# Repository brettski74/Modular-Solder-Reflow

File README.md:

# Modular-Solder-Reflow
Modular designs for a DIY solder reflow hotplate, controller, power supply and more.

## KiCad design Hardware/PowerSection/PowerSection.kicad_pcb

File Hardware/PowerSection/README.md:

# Power Section Design

This directory contains a design for the main power control section of a reflow hotplate. The design is based on a buck converter with a low side switch. It includes current sensing via two INA180 current sense amplifiers. The PWM signal is provided externally. The main goals of the current design are:

  - Verify the design works.
  - Reduce current ripple and voltage spikes to manageable levels.
  - Allow high frequency operation without making input capacitors or other components excessively hot.
  - Allow testing of different microcontroller, screen and UI combinations with a working power section.
  - Provide up to 100W of output power.
  - Be able to operate from power supplies ranging from 12V to 20V DC.

## How to Use This Module

This module provides the power section of a hotplate only. It provides a means for efficient power conversion. It does not supply the control system (ie. microcontroller and firmware), the user interface (eg. screen and buttons or rotary encoder) or the load (ie. the heating element). You need to provide these. Further modules will become availableas the design progresses, although the modular nature also means that you can provide your own.

### Heat Considerations

While care has been taken to design a reasonably efficient design and use components rated for the required currents and they have been mounted with ample board space to help dissipate any heat, this module does handle reasonably large amounts of power. Some of that power will be dissipated in parts of the board and so it may get warm. The board is not yet tested, so you should take appropriate care when testing the board for your own needs and monitor the temperature of its components until you're satisfied that it can adequately handle the heat for your use case.

### Connections

The module includes the following connections:

|| Connector   | Pin  | Description |
| :--- | :---        | :--- | :---        |
|| Barrel Jack |      | Input power. 12V minimum. 18-20V preferred. Note that the Digikey part is rated for up to 8A. The LCSC part is rated for up to 7A. 5.5 x 2.5mm barrel connector. Centre pin positive.|
|| 12-20V      |      | Alternate connection for external power positive terminal via an M3 ring connector or similar. |
|| GND         |      | Alternate connection for external power negative terminal via an M3 ring connector or similar. Grounded. |
|| Htr+        |      | Positive connection for the heating element. |
|| Htr-        |      | Negative connection for the heating element. Note that this is not grounded and must not be connected to the ground connections of this board. |
|<td rowspan=5>J1</td>| PWM  | PWM signal. The gate driver is inverting, so the PWM signal must be active low. When the PWM signal is below about 0.8V, the main MOSFET switch will be on. When this voltage is above about 2.5V, the main MOSFET switch will be off. It does have a 10k pullup to _Vin_, so if left floating should ensure that the main MOSFET switch is off. |
|| Vin  | Supply voltage for the control board. This is used to power current sense and pullups for the gate drive input to ensure compatibility with the microcontroller. Must be between 3.0 and 5.5V. |
|| Ihi  | Current sense output for heating element current used for measuring high magnitude currents. Assuming a 15 $m\Omega$ shunt, voltage should be approximately $V_{Ilo} = 0.015 \times 20 \times I_{htr}$. Output is limited to approximately _Vin_. |
|| Ilo  | Current sense output for heating element current used for measuring low magnitude currents. Assuming a 15 $m\Omega$ shunt, voltage should be approximately $V_{Ilo} = 0.015 \times 200 \times I_{htr}$. Output is limited to approximately _Vin_. |
|| GND  | Ground connection for control board. |
|<td rowspan=5>J2</td>| VS   | Auxiliary connection for supplying power to external boards. This is not intended as an input pin and cannot safely supply the power requirements of the heating element. It is intended as an output to potentially feed power to other boards that may require it. For example, if you don't have some other power supply for your control board, you could feed this into a 3 terminal regulator to provide a steady 5V or 3.3V supply to your control board. |
|| GND  | Auxiliary ground connection for supplying power to external boards. The same power limitations and expected uses for _J2-VS_ also apply to this pin. |

A basic diagram of minimal connections to this module is shown below. A more typical setup would may also include additional items such as a screen, buttons/rotary encoder for input, voltage divider for measuring input voltage, thermistor or other temperature sensor connections and the like.

### Hotplates

The modular design of this board requires that you supply a separate hotplate. While this does mean that you have more separate pieces to connect and potential higher expense to have them produced, it does provide the following advantages:

  - Larger size/lower cost. If working with the cheap Chinese based board manufacturers like JLCPCB, PCBWay, Elecrow and the like, prices are extremely cheap if you can keep under 100mm x 100mm in size. With this pricing, you should be able to produce a board like this plus a 100mm x 100mm hotplate board more cheaply than you could have an integrated board with a hotplate this size included. The integrated board therefore either requires more money or must sacrifice hotplate size to stay cheap.
  - Replaceable hotplate. While it's still unclear just how durable PCB based hotplates may be, we do expect them to eventually wear out from the thermal cycling they will be put through. Having a separate hotplate PCB with minimal electronics attached makes them easier and cheaper to replace when they do wear out.
  - Thermal isolation. A separate hotplate PCB can be more easily and more effectively isolated from the rest of the system without the need to take up valuable board space with cut-outs or other design features to keep the heat of the hotplate away from control and user interface components.

The power module connects to the hotplate via two M3 ring connector terminals on the right side of the board. These can also be used as mounting holes for the board provided that they are being mounted into a non-conductive base. A suggested option is to use a 3D printed base of some sort in ABS or PLA. Care should be taken to ensure sufficient thermal isolation of the base from heat that may be produced in the power module and the hotplate. 

Cables connecting the power module and hotplate should be of sufficient weight to handle the currents involved. They should also use appropriate insulation to handle any thermal leakage from the hotplate into the wires. A minimum suggested spec would be 16AWG stranded copper wire with silicone insulation.

It is recommended to use mechanical connectors for the connections to your hotplate as well. M3 ring connectors are my preferred solution. These avoid problems with plastic or soldered connections which may melt from the heat of the hotplate. After all, the hotplate is intended to get hot enough to melt various solder alloys.

If you currently have spare boards from building a V2.4 or V3.0 board of the AfterEarthLtd hotplate design, you can use one of those as an external hotplate for this board if you have nothing better. You can connect wires directly to the heating element by soldering them onto the board. One should connect to the MOSFET drain terminal (the large one). The other should connect to lower terminal (ie. closest to the heating element) of either C7, D2 or both. If possible, use a higher temperature solder alloy for these connections such as SAC305 (the usual lead-free alloy of tin-silver-copper used in electronics). This should help prevent these connections from desoldering themselves during a reflow cycle.

### Controller

The current design does not yet include a controller. You will need to provide your own. In the absence of a more bespoke design, the suggestion is to use a typical prototyping board like one of the various Arduino modules, Seeeduino Xiao, STM32 Blue Pill, WEMOS S2 Mini or similar boards. My original work with this module will work with Arduino Nano, Seeeduino Xiao and Blue Pill boards. I have most experience with the Nano and the Xiao, although my long term goal is to use STM32 microcontrollers for controlling these hotplates. My plan is to make the firmware modular as well and easily ported to different microcontroller platforms, sensor suites and user interfaces. Until that is done, you are welcome to experiment with this board and with building your own firmware.

J1 should provide most of the connections you may require for the microcontroller to this power module. It is designed as a 5 pin JST-XH connector or compatible. Alternatively, you could also use a 0.1" pin header for connection if you already have those conveniently available. The _PWM_, _Vin_ and _GND_ pins must be connected. _Ihi_ and _Ilo_ can be used for sensing the heating element currents which can be used in conjunction with the heating element voltage to deduce heating element resistance and use it as a temperature sensor. If you also wish to monitor supply voltage, you can feed J2 to an off-board voltage divider to measure that as well. These connections should all be low current/power and should be possible to build on a solderless breadboard for prototyping purposes.

## Theory Of Operation

In addition to the main power input, this board expects a PWM signal at a frequency between 60kHz and 200kHz. The gate drive circuitry is inverting, so the PWM pin is active low. Users must bear this in mind when developing software to control this board. The PWM signal can operate on 3.3V or 5V. It is first fed into MOSFET Q1, which provides level shifting in conjunction with R5. This pulls the PWM signal up to near the main power supply voltage. This is one of the reasons for the 20V upper limit on the input voltage. Most MOSFETs are limited to about 20V on their gate.

The level shifted PWM signal is then fed into a totem pole gate driver (U4) to drive larger currents into Q2's gate. Q2 is the main MOSFET switch. When the PWM signal goes low, Q2's gate is driven high, turning it on. Once Q2 turns on, it pulls current through the heating element and L2. When the PWM signal goes high again, Q2's gate is pulled low, turning it off. Diode D3 now starts to conduct providing a conduction path for the current in L2. L2 limits current ripple in the heater circuit. Capacitor C9 reduces voltage ripple.

C8 and R10 form an RC snubber across the main MOSFET switch. Component values are approximate and not specifically tuned for this design yet. That said, it is expected that they should function adequately for the task. There is also an RC snubber across D3 formed by R8 and C7.

Resistors R11, R12 and R13 form a current shunt for measuring the current through the heating element. The three 45m$\Omega$ resistors form a 15m$\Omega$ shunt. These resistors should have a low temperature coefficient of resistance. Three 2W resistors are specified to provide ample headroom to dissipate heat when operating at high currents - as may be necessary for 12V supplies.

The design includes two current sense amplifiers with different gains to allow for full range current sensing while also allowing higher resolution at lower currents. The current sense amplifier outputs have a low pass filter on their outputs formed by R1/C3 and R2/C4. As designed, these have a corner frequency at about 1.6kHz. It is assumed that PID control would use a sample frequency somewhere in the vicinity of 20-50Hz,

The input currently includes a 10 amp fuse to protect against overcurrent faults. It also includes an input LC filter to help limit upstream impacts from the operation of the heater control.

## Optional Components

The RC snubbers formed by C8/R10 and C7/R8 are not entirely necessary for the ciruit to work, however, they should reduce ringing and other transient effects from the high frequency switching of large currents.

Diode D1 provides a lower impedance path for discharge Q2's gate at turn-off time. While this is usually desirable, the circuit will likely work ok without it.

If you have no intention of measuring the heater current, you can omit the INA180 current sense amplified and associated buffer and filter components. You do need to either include R11, R12 and R13 or alternatively short them with some wire suitable for the current you expect to drive with this board.

Inductor L1 may not ne necessary. It's main purpose is to reduce the amount of noise fed back to the upstream power supply, however, the board will likely work relatively fine without it. If not used, simply short the contacts for L2 with some wire.

## 3D Models

To render a 3D representation of the board and components, some of the footprints require 3D models that are not available with KiCad and are also not included in the git repository. There are freely available 3D models for these components, but since I'm not sure of the licensing of these models, I'm reluctant to include them and effectively be redistributing them in my git repository. Instead, I've included a shell script in the 3d subdirectory that will download the models from publicly accessible locations on the web for you to use for your own needs. If you don't care about a 3D rendering of the board and components, then you don't need these 3D models.

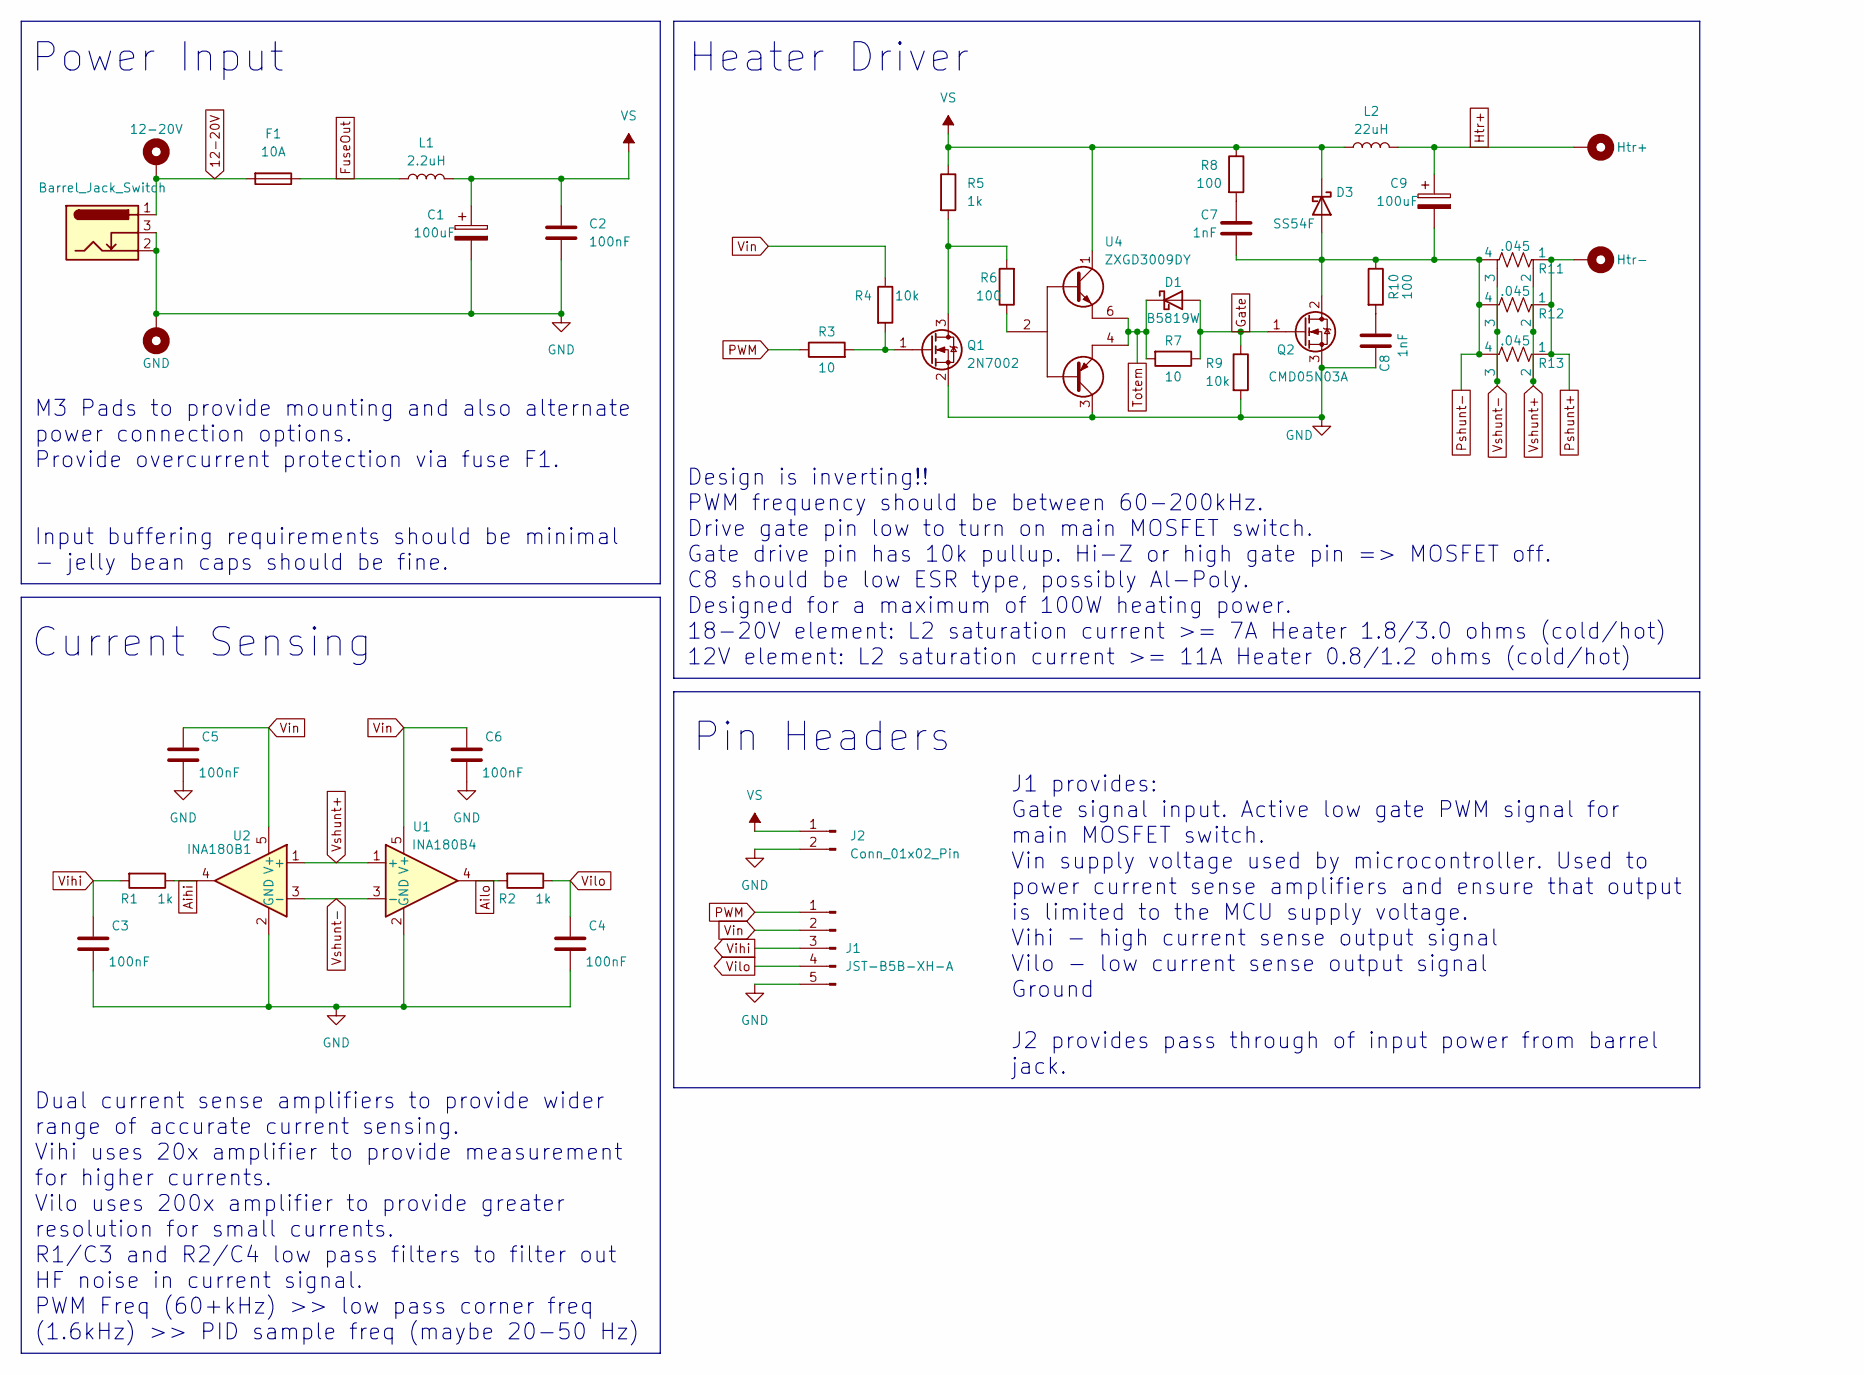
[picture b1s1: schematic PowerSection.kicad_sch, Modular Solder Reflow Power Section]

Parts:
12V1: Barrel_Jack_Switch; BarrelJack_GCT_DCJ200-10-A_Horizontal; LCSC Part C5155560
C1, C9: 100uF; CP_Elec_8x10.5; LCSC Part C454651
C2, C3, C4, C5, C6: 100nF; C_0603_1608Metric
C7: 1nF; R_0603_1608Metric
C8: 1nF; C_0603_1608Metric
D1: B5819W; D_SOD-123; LCSC Part C2943878
D3: SS54F; D_SMBF; LCSC Part C2922187
F1: 10A; R_1206_Fuse; LCSC Part C207003
H1, H2: MountingHole_Pad; MountingHole_3.2mm_M3_Pad_Via
H3, H4: Heater Pad; MountingHole_3.2mm_M3_Pad_Via
J1: JST-B5B-XH-A; JST_XH_B5B-XH-A_1x05_P2.50mm_Vertical; LCSC Part C722877
J2: Conn_01x02_Pin; PinHeader_1x02_P2.54mm_Vertical; LCSC Part C2894925
L1: 2.2uH; L_12x12-ish; LCSC Part C2921227
L2: 22uH; L_25x15_FlatWire; LCSC Part C2761965
Q1: 2N7002; SOT-23; LCSC Part C2898356
Q2: CMD05N03A; TO-252-2; LCSC Part C5203816
R1, R2, R5: 1k; R_0603_1608Metric
R3, R7: 10; R_0603_1608Metric
R4, R9: 10k; R_0603_1608Metric
R6, R8, R10: 100; R_0603_1608Metric
R11, R12, R13: .045; R_2512_Kelvin_Shunt; LCSC Part C2683379
U1: INA180B4; SOT-23-5; LCSC Part C1879708
U2: INA180B1; SOT-23-5; LCSC Part C544664
U4: ZXGD3009DY; SOT-363_SC-70-6; LCSC Part C441818

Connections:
12-20V: 12V1.1, F1.2, H1.1
Aihi: R1.1, U2.4
Ailo: R2.2, U1.4
FuseOut: F1.1, L1.1
GND: 12V1.2, 12V1.3, C1.2, C2.2, C3.2, C4.2, C5.2, C6.2, C8.2, H2.1, J1.5, J2.2, Q1.2 (S), Q2.3 (S), R9.2, U1.2 (GND), U2.2 (GND), U4.3 (Vee)
Gate: D1.2 (A), Q2.1 (G), R7.1, R9.1
Htr+: C9.1, H3.1, L2.2
unnamed: C7.1, R8.2
unnamed: C8.1, R10.2
unnamed: Q1.3 (D), R5.2, R6.2
unnamed: Q1.1 (G), R3.2, R4.2
unnamed: R6.1, U4.2 (B)
PWM: J1.1, R3.1
Pshunt+: H4.1, R11.1, R12.1, R13.1
Pshunt-: C7.2, C9.2, D3.2 (A), Q2.2 (D), R10.1, R11.4, R12.4, R13.4
Totem: D1.1 (K), R7.2, U4.4 (Sink), U4.6 (Source)
VS: C1.1, C2.1, D3.1 (K), J2.1, L1.2, L2.1, R5.1, R8.1, U4.1 (Vcc)
Vihi: C3.1, J1.3, R1.2
Vilo: C4.1, J1.4, R2.1
Vin: C5.1, C6.1, J1.2, R4.1, U1.5 (V+), U2.5 (V+)
Vshunt+: R11.2, R12.2, R13.2, U1.1 (+), U2.1 (+)
Vshunt-: R11.3, R12.3, R13.3, U1.3 (-), U2.3 (-)

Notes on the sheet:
Design is inverting!! PWM frequency should be between 60-200kHz. Drive gate pin low to turn on main MOSFET switch. Gate drive pin has 10k pullup. Hi-Z or high gate pin => MOSFET off. C8 should be low ESR type, possibly Al-Poly. Designed for a maximum of 100W heating power. 18-20V element: L2 satura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
Dual current sense amplifiers to provide wider range of accurate current sensing. Vihi uses 20x amplifier to provide measurement for higher currents. Vilo uses 200x amplifier to provide greater resolution for small currents. R1/C3 and R2/C4 low pass filters to filter out HF noise in current signal.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
M3 Pads to provide mounting and also alternate power connection options. Provide overcurrent protection via fuse F1. Input buffering requirements should be minimal - jelly bean caps should be fine.
J1 provides: Gate signal input. Active low gate PWM signal for main MOSFET switch. Vin supply voltage used by microcontroller. Used to power current sense amplifiers and ensure that output is limited to the MCU supply voltage. Vihi - high current sense output signal Vilo - low current sense output 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
Power Input
Pin Headers
Heater Driver
Current Sensing

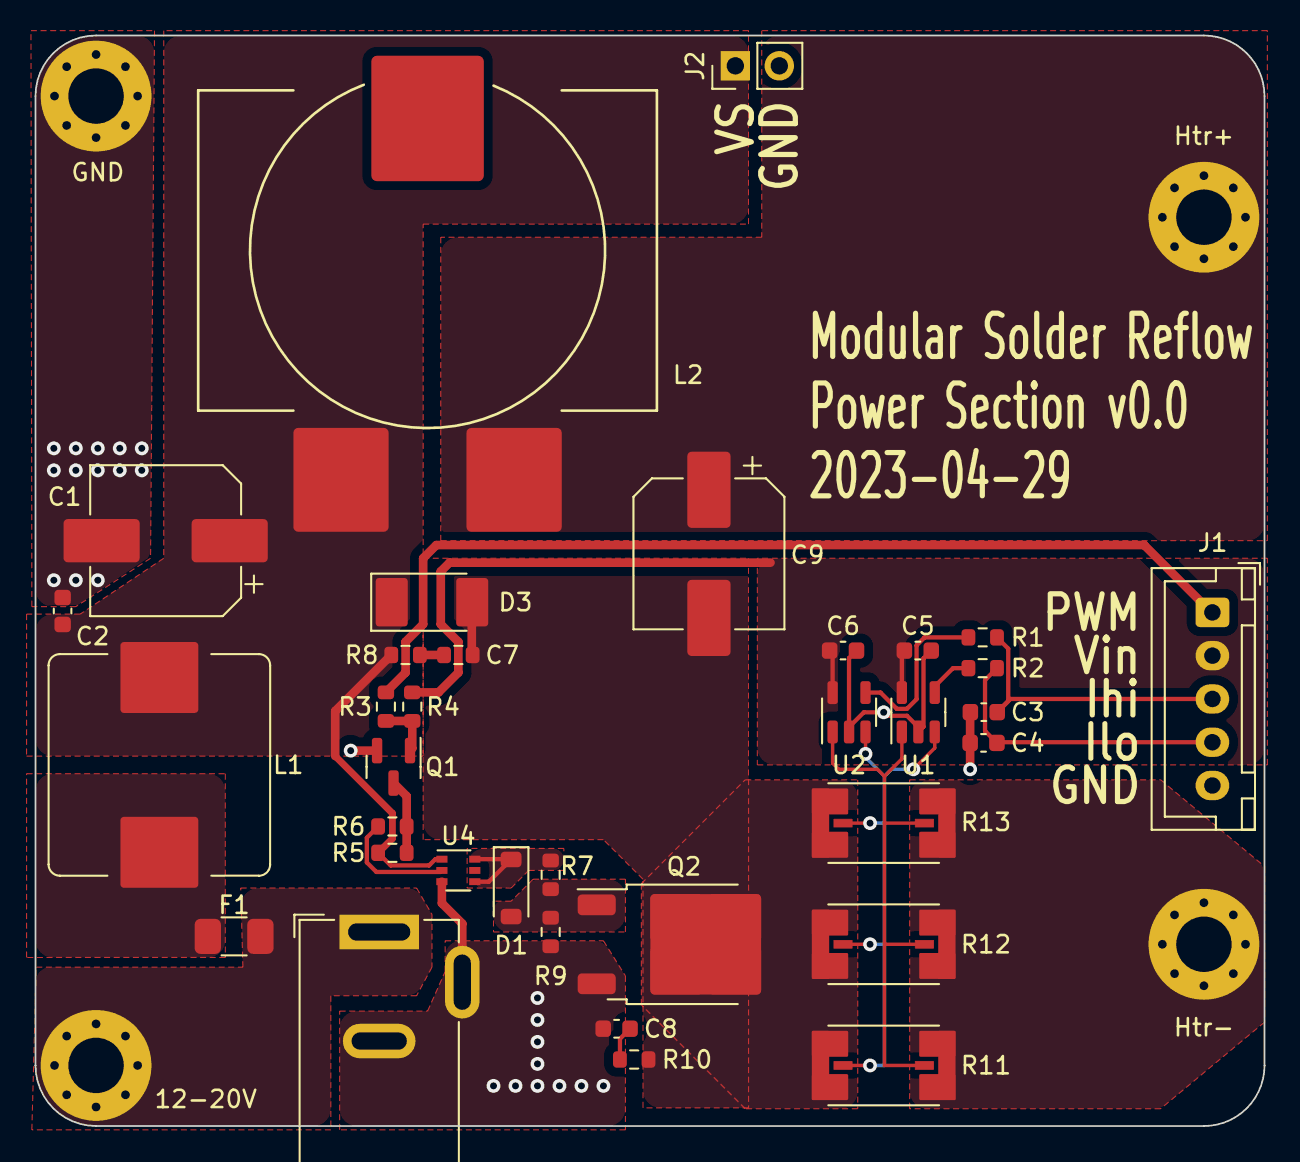
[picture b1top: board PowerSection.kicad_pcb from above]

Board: 2 copper layers, 71.0 x 63.0 mm, 39 parts (0 on the bottom side), 22 nets.

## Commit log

2023-04-26 Updated licensing to use CERN-OHL-W for hardware and GPLv2 for everything else.
2023-04-26 Initial commit of power section schematic and LTSpice model.
2023-04-26 Added hardware readme file.
2023-04-26 Annotated some parts with LCSC and Digikey part numbers. Updated spice model to match reference designators in the Kicad schematic.
2023-04-27 Replaced custom global symbols with standard KiCad symbols or local project symbols.
2023-04-28 Updated footprints to use standard or project local footprints. Updated component specs to handle 12V 100W hotplates - beefier inductors. Added input ripple filter inductor.
2023-04-28 Fixed inductor reference designators on PowerSection design.
2023-04-29 Initial rough layout completed, with minor schematic changes to address layout challenges.
2023-04-29 Minor tweaks - labeling contacts and such.
2023-04-29 Fixed design rule checker violations and unconnected fill zone for Vin on U1.
2023-04-29 Plotted Power Section PCB v0.0 for JLCPCB fabrication.
2023-04-29 Added missing vias for ground fills. Added specifications text on the back of the board.
2023-04-29 Initial pass at readme file for Power Section Design Updated 3d models for the inductors and barrel jack.
2023-04-29 Noted L1 is optional.
2023-04-29 Added script to download 3d models from Digikey website.
2023-04-30 Added note about 3D model downloads to the README.
2023-04-30 Added more usage information for the power module in README.md.
2023-04-30 Update README.md
    Modified table to have rowspans using HTML workaround.
2023-04-30 Fixed italics in README.md for Hardware/PowerSection.
2023-04-30 Fixed milliohm unit symbols in Hardware/PowerSection/README.md.
2023-05-01 Fixed a couple of typos in the Hardware/PowerSection/README.
2023-05-01 Fixed a typo properly this time!
2023-05-03 Added basic connections diagram from Fritzing.
2023-05-03 Added PNG fritzing image as SVG was missing components.
2023-05-03 Added connection diagram to PowerSection README
